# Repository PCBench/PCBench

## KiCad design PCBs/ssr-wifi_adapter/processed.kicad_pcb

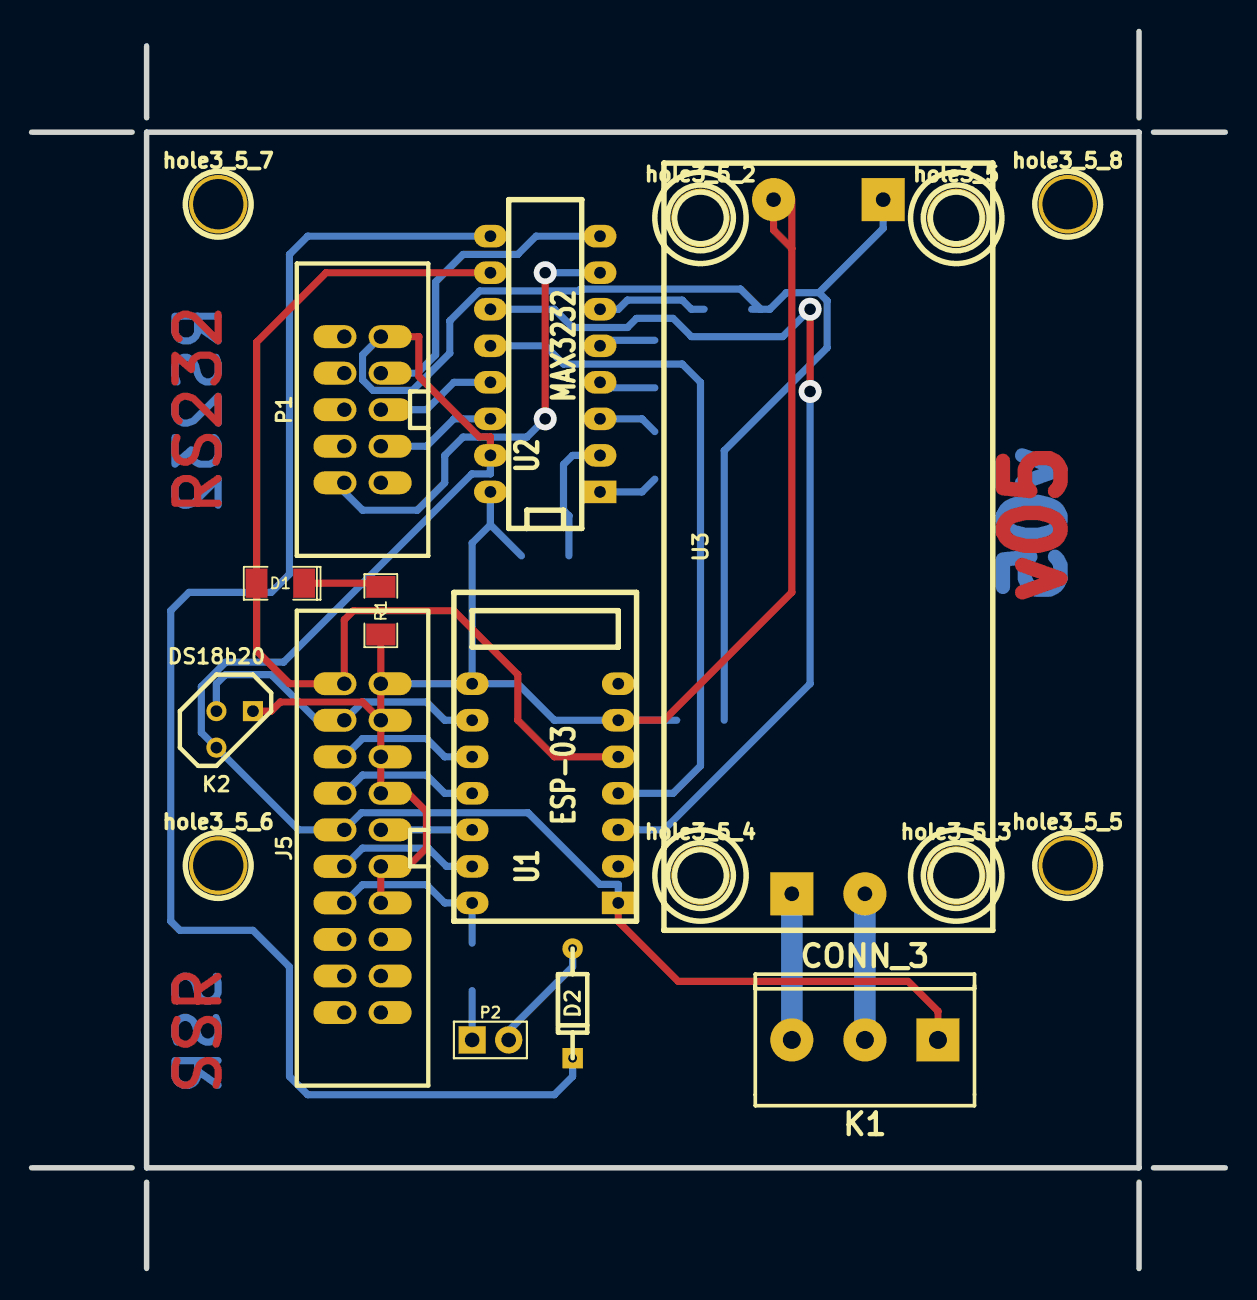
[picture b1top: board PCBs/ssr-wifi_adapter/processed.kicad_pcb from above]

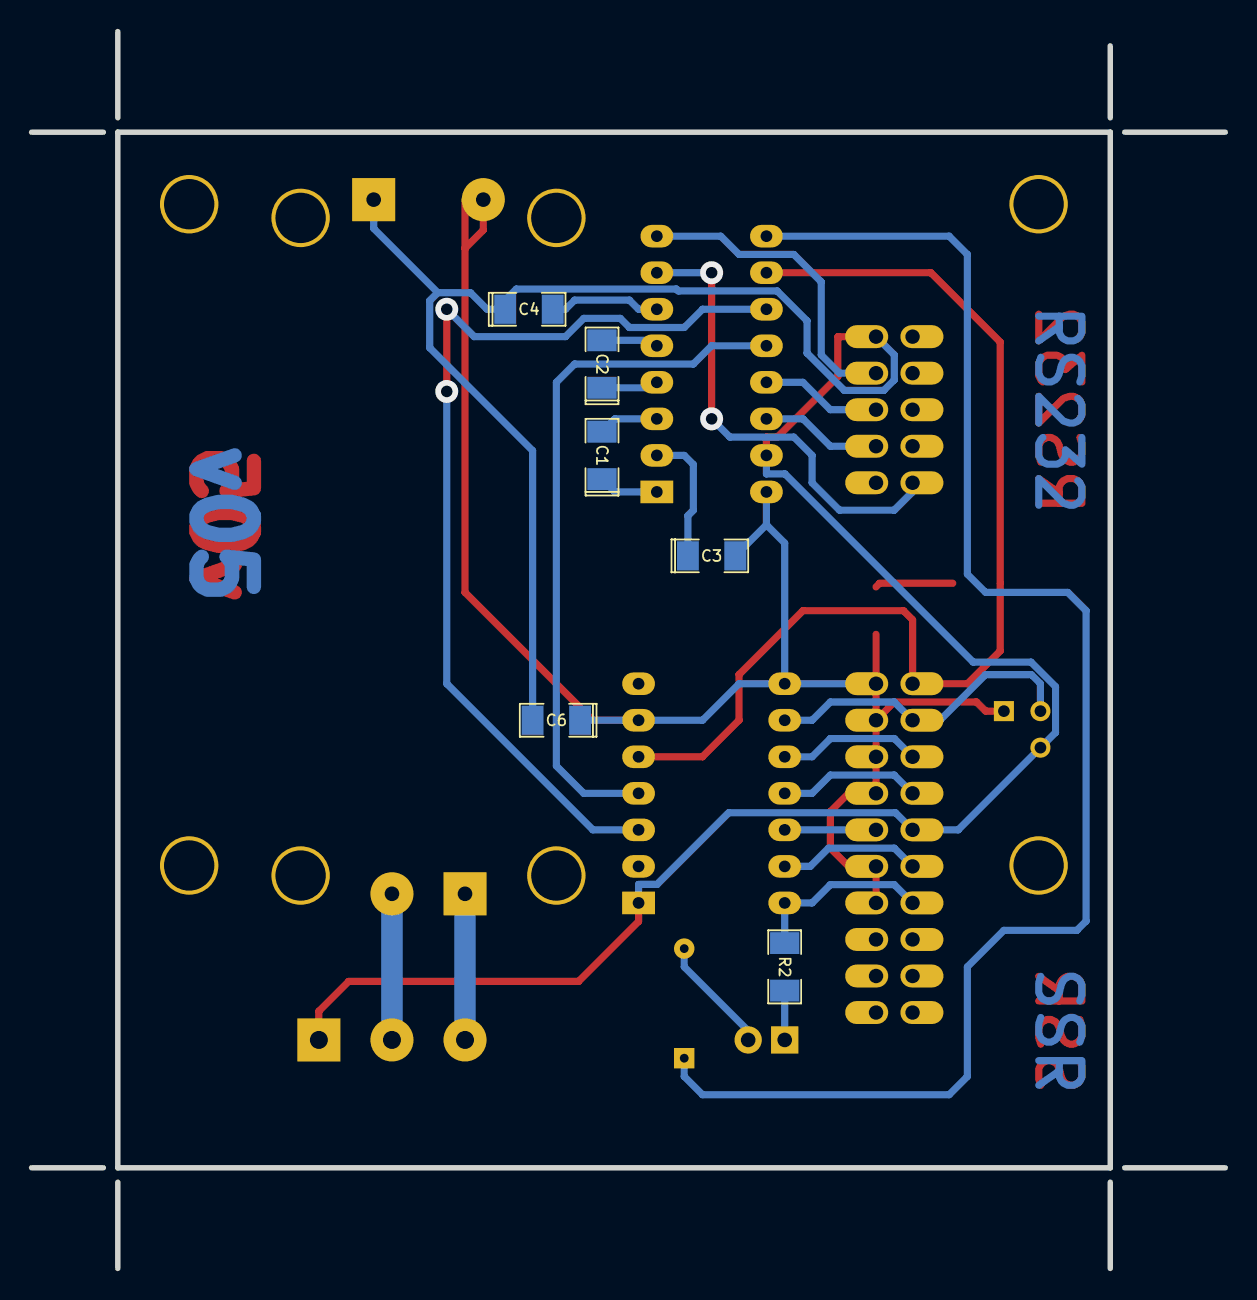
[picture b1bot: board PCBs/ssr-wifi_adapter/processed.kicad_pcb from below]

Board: 2 copper layers, 69.0 x 72.0 mm, 25 parts (6 on the bottom side), 27 nets.

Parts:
C1, C2, C3, C4, C6: 1uF; SM1206POL
D1: LED_RED; SM1206POL
D2: DIODESCH; DO-35
J5: CONN_10X2; conn_strip_10x2_largepads
K1: CONN_3; mors_3p
K2: DS18b20; TO92-123
P1: CONN_5X2; conn_strip_5x2_largepads
P2: FLASH; PIN_ARRAY_2X1
R1: 390; SM1206
R2: 47; SM1206
U1: ESP-03; ESP03BB
U2: MAX3232; DIP-16__300_ELL
U3: SWITCHER; SWITCHER_3V3_1A
hole3_5, hole3_5_2, hole3_5_3, hole3_5_4, hole3_5_5, hole3_5_6, hole3_5_7, hole3_5_8: 3.5mm; hole3_5

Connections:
+3.3V: C3.2, C6.1, J5.7, J5.9, J5.13, J5.15, J5.17, J5.19, K2.3, R1.2, U1.6, U1.8, U2.16, U3.3
/BOOT: D2.2, U2.9
/DSR: P1.2, U2.7
/DTR: P1.7, U2.8
/L: K1.3, U3.1
/LED: D1.2, J5.20, U1.5, U2.10
/N: K1.2, U3.2
/RXD: P1.3, U2.14
/SSR0: J5.8, R2.1, U1.14
/SSR1: J5.10, U1.13
/SSR2: J5.11, U1.12
/SSR3: J5.14, U1.11
/SSR4: J5.16, U1.10
/SSR5: J5.18, K2.2, U1.9
/TXD: P1.5, U2.13
/URXD: U1.4, U2.12
/UTXD: U1.3, U2.11
GND: C4.1, C6.2, J5.12, K1.1, K2.1, P1.9, U1.1, U2.15, U3.4
unnamed: D2.1, P2.2
unnamed: P2.1, R2.2
unnamed: D1.1, R1.1
unnamed: C2.1, U2.4
unnamed: C2.2, U2.5
unnamed: C3.1, U2.2
unnamed: C4.2, U2.6
unnamed: C1.1, U2.1
unnamed: C1.2, U2.3

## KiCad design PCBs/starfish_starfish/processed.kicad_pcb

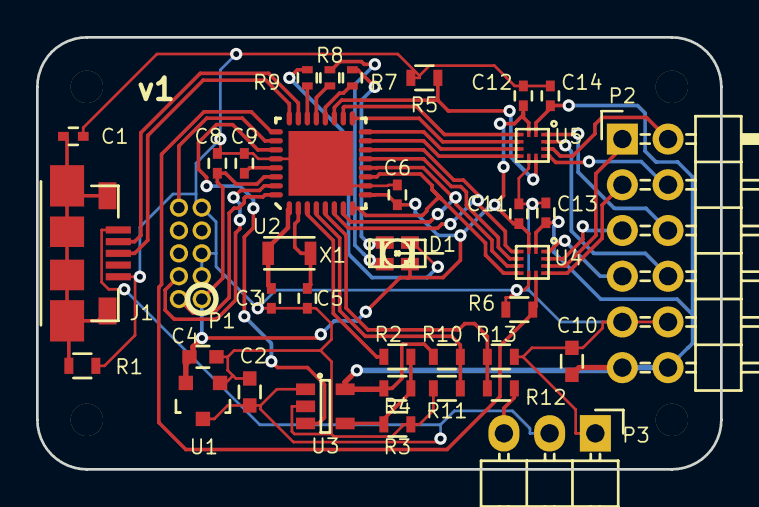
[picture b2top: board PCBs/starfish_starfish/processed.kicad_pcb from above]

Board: 2 copper layers, 38.0 x 24.0 mm, 37 parts (0 on the bottom side), 43 nets.

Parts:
C1, C3, C5: 10pF; C_0402
C2, C4, C10: 1uF; C_0603
C6, C8, C9, C11, C12, C13, C14: 100nF; C_0402
D1: LED-RGB-COMMON-ANODE; LED-1206-RGB
J1: microUSB; MICRO-USB-10104111
P1: CONN_02X05; CONN_02x05_0.05in
P2: CONN_6X2; Pin_Header_Angled_2x06
P3: CONN_3; Pin_Header_Angled_1x03
R1, R2, R10, R12: 47k; R_0603
R3, R4, R5, R6, R11, R13: 27k; R_0603
R7, R8, R9: 120; R_0402
U1: AP2120N; SOT-23
U2: SAMD21E15A-MU; QFP32
U3: TPS73101; SOT-23-5
U4, U5: FXMAR2104; UMLP-12
X1: CRYSTAL; FC-135

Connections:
+3V3: C4.1, C6.1, C8.1, C11.1, C12.1, D1.4, P1.1, U1.2, U2.9, U2.30, U4.2, U5.2
+5V: C2.1, J1.1, P3.2, U1.3, U3.1
/ADC: R12.2, R13.1, U2.5
/ADC_IN: P3.3, R12.1
/ADC_P: R10.2, R11.1, U2.4
/DAC: R4.1, U2.3
/EN_P: U2.27, U3.3
/EN_X: R6.1, U2.25, U4.8
/EN_Y: R5.1, U2.19, U5.8
/LED_B: R9.2, U2.22
/LED_G: R8.2, U2.21
/LED_R: R7.2, U2.20
/SWCLK: P1.4, U2.31
/SWDIO: P1.2, U2.32
/USB+: J1.3, U2.24
/USB-: J1.2, U2.23
/X1: P2.1, U4.10
/X1M: U2.7, U2.12, U4.5
/X2: P2.3, U4.9
/X2M: U2.8, U2.11, U4.6
/X3: P2.5, U4.11
/X3M: U2.13, U4.4
/X4: P2.7, U4.12
/X4M: U2.6, U2.14, U4.3
/Y1: P2.2, U5.10
/Y1M: U2.16, U5.5
/Y2: P2.4, U5.9
/Y2M: U2.15, U5.6
/Y3: P2.6, U5.12
/Y3M: U2.18, U5.3
/Y4: P2.8, U5.11
/Y4M: U2.17, U5.4
/~RESET: P1.10, U2.26
GND: C1.2, C2.2, C3.2, C4.2, C5.2, C6.2, C8.2, C9.2, C10.2, C11.2, C12.2, C13.2, C14.2, J1.5, P1.3, P1.5, P1.9, P2.9, P2.10, P3.1, R1.2, R3.2, R5.2, R6.2, R11.2, R13.2, U1.1, U2.0, U2.10, U2.28, U3.2, U4.7, U5.7
unnamed: C1.1, J1.0, R1.1
unnamed: C3.1, U2.1, X1.1
unnamed: C5.1, U2.2, X1.2
unnamed: C9.1, U2.29
unnamed: D1.1, R9.1
unnamed: D1.2, R7.1
unnamed: D1.3, R8.1
unnamed: R2.2, R3.1, R4.2, U3.4
VAA: C10.1, C13.1, C14.1, P2.11, P2.12, R2.1, R10.1, U3.5, U4.1, U5.1

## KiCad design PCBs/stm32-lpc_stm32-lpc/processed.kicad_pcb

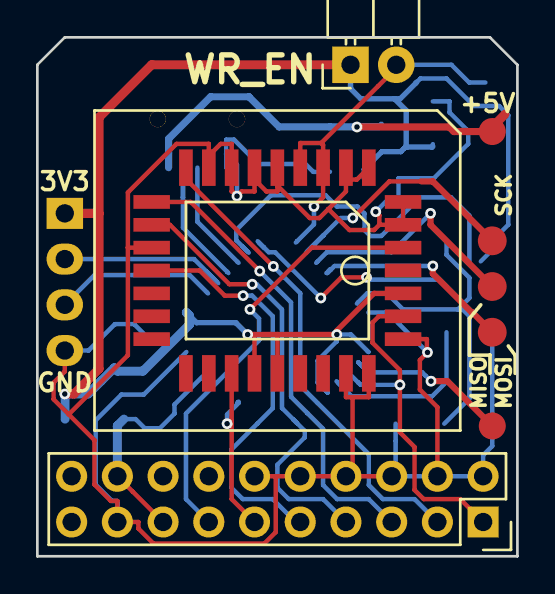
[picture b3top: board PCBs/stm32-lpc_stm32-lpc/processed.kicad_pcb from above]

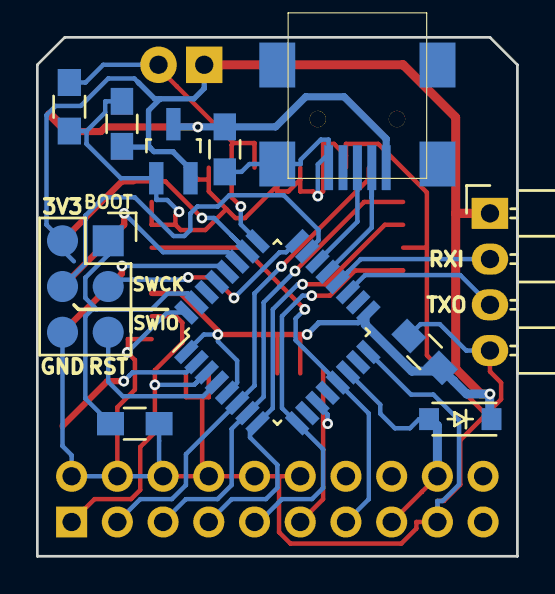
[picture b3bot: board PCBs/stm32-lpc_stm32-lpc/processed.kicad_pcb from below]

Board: 2 copper layers, 26.7 x 28.8 mm, 19 parts (11 on the bottom side), 24 nets.

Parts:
C1, C2, C3: 1u; C_0805_HandSoldering
CON1: SWD_BOOT_CS-6; Socket_Strip_Straight_2x03
D1: D_Schottky_Small; SOD-123
JP1: JUMPER; Pin_Header_Angled_1x02
P1: CONN_02X10; Socket_Strip_Straight_2x10
P2: CONN_01X04; Pin_Header_Angled_1x04
P3: USB_OTG; USB-MINI-B-SMD
P4, P5, P6, P7, P8: CONN_01X01; TSTPT
R1, R2: 4k7; R_0805_HandSoldering
U1: Pm49FL004; PLCC-32
U2: STM32F042Kx; LQFP-32_7x7mm_Pitch0.8mm
U3: MCP1700; SOT-23_Handsoldering

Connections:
/3V3IN: D1.2, P1.15, P1.18, U2.14
/BOOT0: CON1.1, R2.1, U2.31
/CLK: P1.1, U1.31, U2.3
/D0: P1.3, U1.13, U2.6
/D1: P1.5, U1.14, U2.7
/D2: P1.7, U1.15, U2.8
/D3: P1.9, U1.17, U2.9
/D+: P3.3, U2.22
/D-: P3.2, U2.21
/MISO: P5.1, U2.27
/MOSI: P4.1, U2.28
/RXD: P2.2, U2.20
/SCK: P6.1, U2.26
/SPIOE: P7.1, U2.2
/SWCLK: CON1.3, U2.24
/SWDIO: CON1.4, U2.23
/TXD: P2.3, U2.19
/VBUS: C2.1, P3.1, P8.1, U3.3
/~LFRAME: P1.11, U1.23, U2.11
/~RST: P1.13, U1.2, U2.13
/~SRST: CON1.5, U2.4
/~WP: JP1.2, R1.1, U1.7, U1.8, U2.25
GND: C1.2, C2.2, C3.2, CON1.6, P1.2, P1.4, P1.6, P1.8, P1.10, P1.12, P1.17, P2.4, P3.5, P3.6, R1.2, R2.2, U1.3, U1.4, U1.5, U1.6, U1.9, U1.10, U1.11, U1.12, U1.16, U1.28, U1.29, U1.30, U2.16, U2.32, U3.1
VCC: C1.1, C3.1, CON1.2, D1.1, JP1.1, P2.1, U1.24, U1.25, U1.32, U2.1, U2.5, U2.17, U3.2

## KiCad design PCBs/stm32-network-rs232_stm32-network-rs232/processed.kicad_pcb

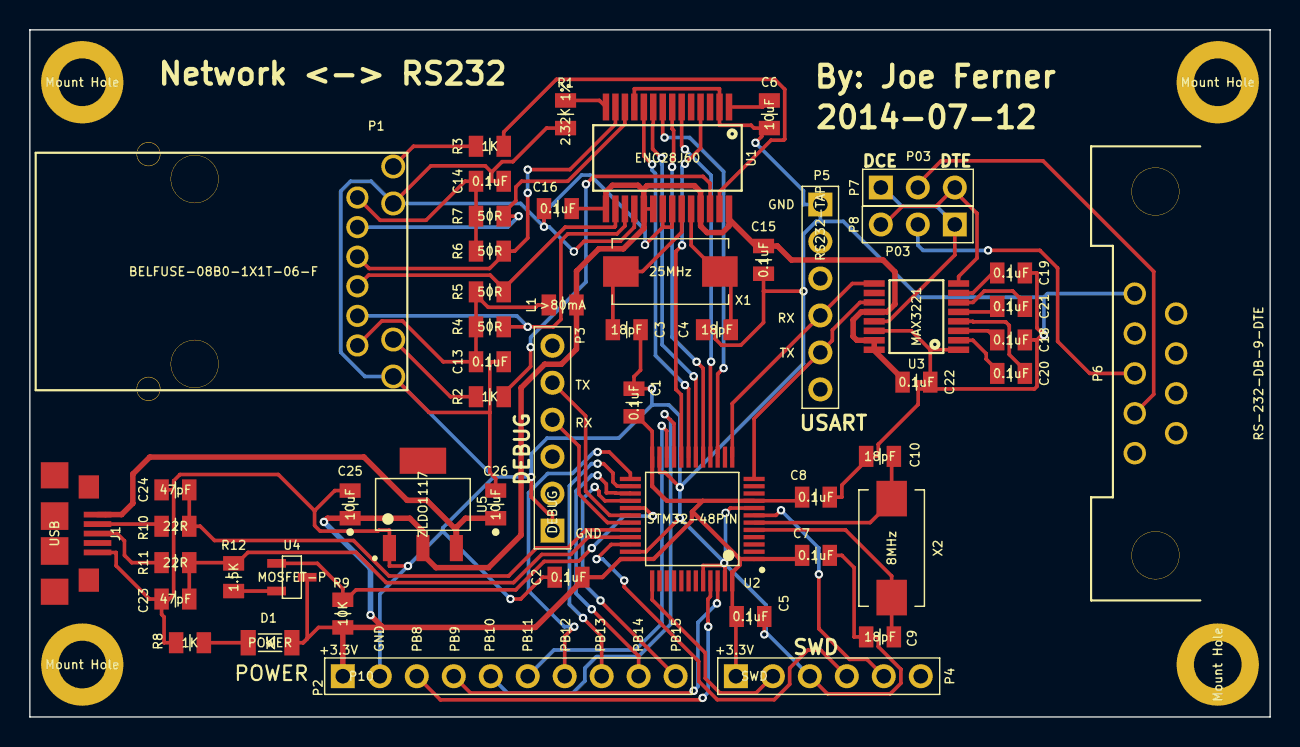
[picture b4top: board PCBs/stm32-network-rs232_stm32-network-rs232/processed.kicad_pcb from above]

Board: 2 copper layers, 85.2 x 47.2 mm, 57 parts (0 on the bottom side), 57 nets.

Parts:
C1, C2, C5, C7, C8, C13, C14, C15, C16, C18, C19, C20, C21, C22: 0.1uF; CAPC2012X100N
C3, C4, C9, C10: 18pF; CAPC2012X100N
C6: 10uF; CAPC2012X100N
C23, C24: 47pF; CAPC2012X100N
C25, C26: 10uF; CAPCP2012X100N
D1: POWER; LEDC3216X100N
J1: USB; JST_UB-MC5BR3-SD204-4S-NMP
L1: >80mA; RESC2012X100N
M1, M2, M3, M4: Mount Hole; MTGNP565H328Z565P
P1: BELFUSE-08B0-1X1T-06-F; BEL-FUSE-08B0-1X1T-06-F
P2: P10; HDRV10W66P254_1X10_1006X249X838P
P3: DEBUG; HDRV6W66P254_1X6_1524X249X838P
P4: SWD; HDRV6W66P254_1X6_1524X249X838P
P5: RS232-TAP; HDRV6W66P254_1X6_1524X249X838P
P6: RS-232-DB-9-DTE; TECONN-5747840-2
P7, P8: P03; HDRV3W66P254_1X3_762X249X838P
R1: 2.32K 1%; RESC2012X100N
R2, R3, R8: 1K; RESC2012X100N
R4, R5, R6, R7: 50R; RESC2012X100N
R9: 10K; RESC2012X100N
R10, R11: 22R; RESC2012X100N
R12: 1.5K; RESC2012X100N
U1: ENC28J60; SOP65P780X200-28N
U2: STM32-48PIN; QFP50P900X900X160-48N
U3: MAX3221; SOP65P640X120-16N
U4: MOSFET-P; SOT95P237X112_123-3N
U5: ZLDO1117; SOT230P700X180-4N
X1: 25MHz; XTAL8045X200N
X2: 8MHz; XTAL8045X200N

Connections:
+3.3V: C1.2, C2.2, C5.2, C7.2, C8.2, C15.2, C16.2, C22.1, C25.1, D1.1, L1.1, P2.1, P4.1, R9.2, U1.15, U1.19, U1.20, U1.25, U1.28, U2.1, U2.9, U2.24, U2.36, U2.48, U3.12, U3.15, U3.16, U4.3, U5.2
+5V: C26.1, J1.1, U5.3
/DB9RX: P6.2, P7.2
/DB9TX: P6.3, P8.2
/ENC28J60CS: U1.9, U2.18
/ENC28J60INT: U1.4, U2.20
/ENC28J60RESET: U1.10, U2.19
/RS232RX: P7.3, P8.3, U3.8
/RS232TX: P7.1, P8.1, U3.13
/SPIMISO: U1.6, U2.16
/SPIMOSI: U1.7, U2.17
/SPISCK: U1.8, U2.15
/SWCLK: P4.2, U2.37
/SWDIO: P4.4, U2.34
/USART1RX: P3.4, U2.31
/USART1TX: P3.5, U2.30
/USART2RX: P5.4, U2.13, U3.9
/USART2TX: P5.5, U2.12, U3.11
/USBDIS: R9.1, U2.29, U4.1
/USBDM: C24.1, R10.1, U2.32
/USBDP: C23.1, R11.1, R12.1, U2.33
/nRST: P4.5, U2.7
GNDPWR: C1.1, C2.1, C3.2, C4.2, C5.1, C6.2, C7.1, C8.1, C9.2, C10.2, C13.1, C14.1, C15.1, C16.1, C18.2, C19.2, C22.2, C23.2, C24.2, C25.2, C26.2, J1.5, P1.7, P1.9, P2.2, P3.1, P4.3, P5.1, P6.5, R1.1, R8.1, U1.2, U1.11, U1.18, U1.21, U1.22, U2.8, U2.23, U2.35, U2.44, U2.47, U3.1, U3.14, U5.1
unnamed: C3.1, U1.23, X1.1
unnamed: C4.1, U1.24, X1.2
unnamed: C6.1, U1.1
unnamed: C9.1, U2.5, X2.1
unnamed: C10.1, U2.6, X2.2
unnamed: C13.2, L1.2, P1.1, R4.1, R5.2
unnamed: C14.2, P1.6, R6.1, R7.2
unnamed: C18.1, U3.3
unnamed: C19.1, U3.7
unnamed: C20.1, U3.2
unnamed: C20.2, U3.4
unnamed: C21.1, U3.5
unnamed: C21.2, U3.6
unnamed: D1.2, R8.2
unnamed: J1.2, R10.2
unnamed: J1.3, R11.2
unnamed: P1.2, R4.2, U1.17
unnamed: P1.3, R5.1, U1.16
unnamed: P1.4, R6.2, U1.13
unnamed: P1.5, R7.1, U1.12
unnamed: P1.8, R2.2
unnamed: P1.10, R3.2
unnamed: P2.3, U2.45
unnamed: P2.4, U2.46
unnamed: P2.5, U2.21
unnamed: P2.6, U2.22
unnamed: P2.7, U2.25
unnamed: P2.8, U2.26
unnamed: P2.9, U2.27
unnamed: P2.10, U2.28
unnamed: R1.2, U1.14
unnamed: R2.1, U1.26
unnamed: R3.1, U1.27
unnamed: R12.2, U4.2

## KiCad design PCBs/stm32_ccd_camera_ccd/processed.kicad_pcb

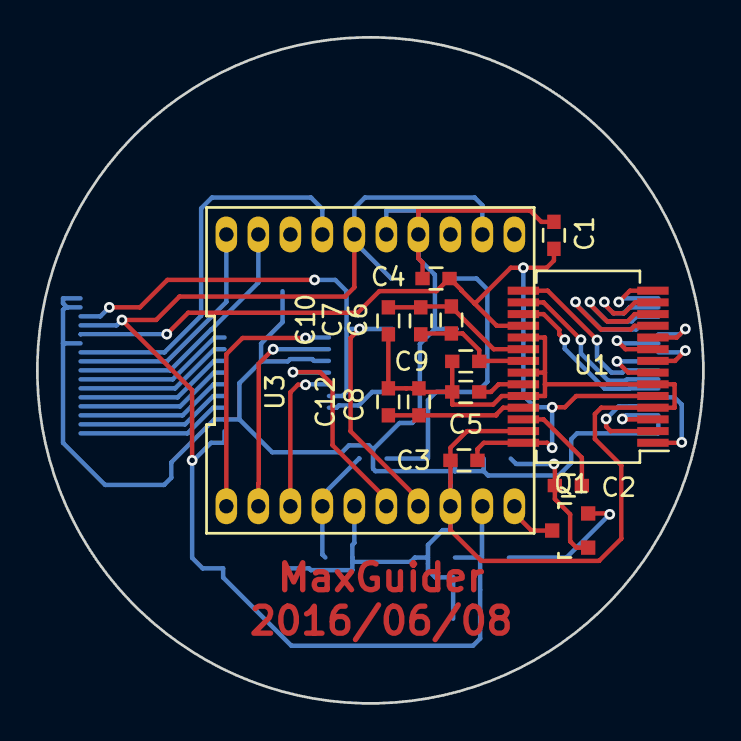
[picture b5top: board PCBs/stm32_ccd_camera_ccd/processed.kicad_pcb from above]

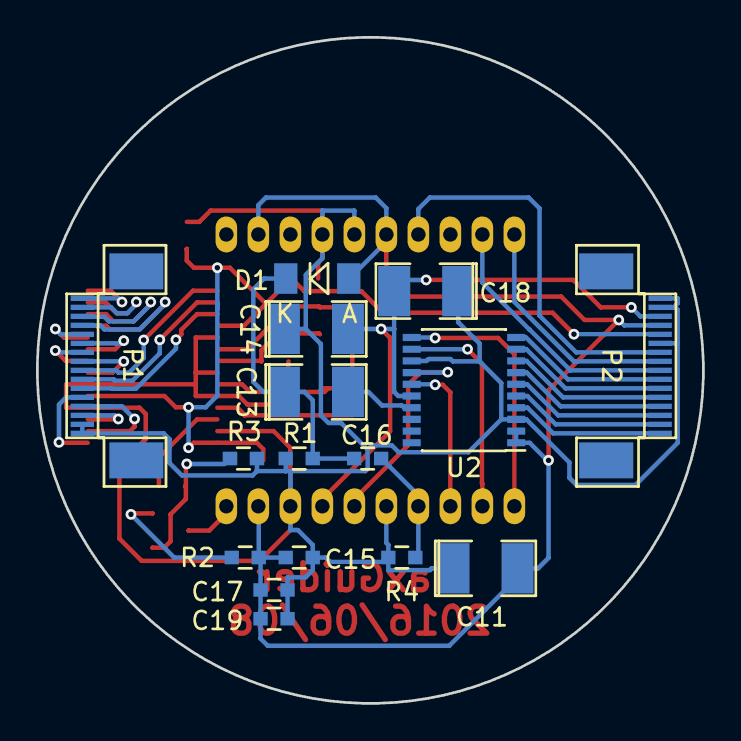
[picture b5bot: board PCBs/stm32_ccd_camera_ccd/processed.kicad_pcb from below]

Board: 2 copper layers, 37.0 x 37.0 mm, 30 parts (16 on the bottom side), 43 nets.

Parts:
C1, C2, C3, C4, C5, C6, C8, C9, C10: 0.1; C_0603
C7: 10; C_0603
C11, C18: 3.3/16V; SMD-1210_Pol
C12, C16: 1; C_0603
C13: 1/35V; SMD-1210_Pol
C14: 22/16V; SMD-1210_Pol
C15, C19: 0.01; C_0603
C17: 3.3/20V; C_0603
D1: D_Small; MiniMELF_Standard
P1, P2: CONN_01X16; FPC_16
Q1: BF862; SOT-23
R1: 100K; C_0603
R2: 100; C_0603
R3: 3.9K; C_0603
R4: 1M; C_0603
U1: AD9826; SSOP-28_5.3x10.2mm_Pitch0.65mm
U2: CXD1267AN; SSOP-20_4.4x6.5mm_Pitch0.65mm
U3: ICX429AL

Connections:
+5V: C1.1, C3.1, C4.2, P2.5, U1.5, U1.18, U1.28
/+15V: C11.2, C15.1, C17.2, C19.2, D1.2, P2.4, R2.2, U2.1, U2.2, U3.9, U3.12, U3.16
/-9V: C14.2, C18.2, P2.3, U2.16, U3.7
/SCLK: P1.7, U1.16
/SDATA: P1.8, U1.15
/SLOAD: P1.6, U1.17
GND: C1.2, C3.2, C4.1, C5.2, C8.2, C9.2, C10.2, C11.1, C12.2, C14.1, C15.2, C17.1, C18.1, C19.1, P1.1, P1.2, P2.1, P2.2, P2.6, R1.2, R3.1, R4.2, U1.4, U1.6, U1.19, U1.22, U1.24, U1.27, U2.3, U2.13, U3.5, U3.8, U3.14, U3.15
unnamed: C2.1, U1.26
unnamed: C2.2, Q1.1, R3.2
unnamed: C5.1, U1.23
unnamed: C6.1, C7.1, C9.1, U1.21
unnamed: C6.2, C7.2, C10.1, U1.20
unnamed: C8.1, C12.1, U1.25
unnamed: C13.1, C16.2, D1.1, R1.1
unnamed: C13.2, U2.17
unnamed: C16.1, R4.1, U3.4
unnamed: P1.3, U1.3
unnamed: P1.4, U1.2
unnamed: P1.5, U1.1
unnamed: P1.9, U1.7
unnamed: P1.10, U1.8
unnamed: P1.11, U1.9
unnamed: P1.12, U1.10
unnamed: P1.13, U1.11
unnamed: P1.14, U1.12
unnamed: P1.15, U1.13
unnamed: P1.16, U1.14
unnamed: P2.7, U3.17
unnamed: P2.8, U3.20
unnamed: P2.9, U3.19
unnamed: P2.10, U2.10
unnamed: P2.11, U2.9
unnamed: P2.12, U2.8
unnamed: P2.13, U2.7
unnamed: P2.14, U2.6
unnamed: P2.15, U2.5
unnamed: P2.16, U2.4
unnamed: Q1.2, R2.1
unnamed: Q1.3, U3.10
unnamed: U2.11, U3.1
unnamed: U2.12, U3.2
unnamed: U2.14, U3.6
unnamed: U2.15, U3.3

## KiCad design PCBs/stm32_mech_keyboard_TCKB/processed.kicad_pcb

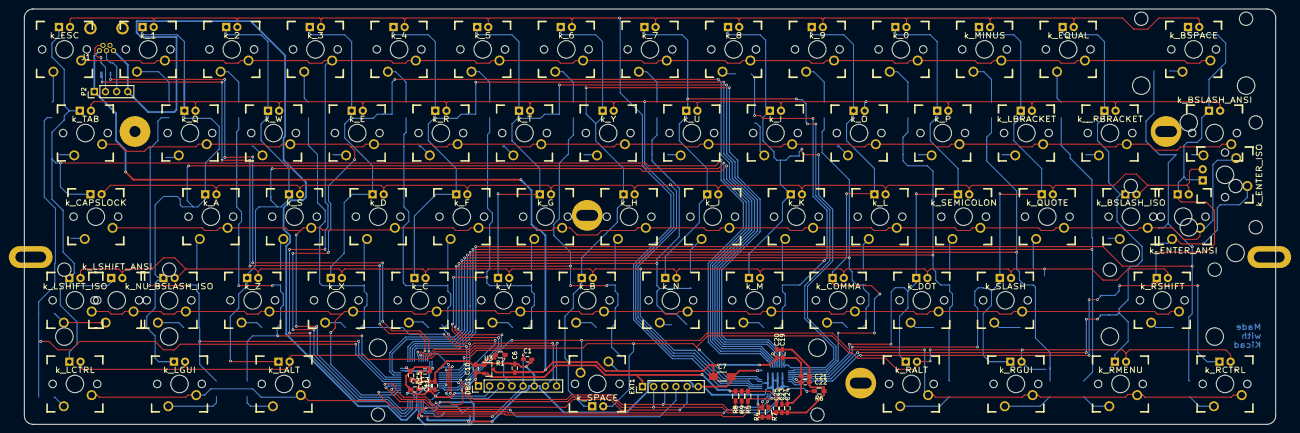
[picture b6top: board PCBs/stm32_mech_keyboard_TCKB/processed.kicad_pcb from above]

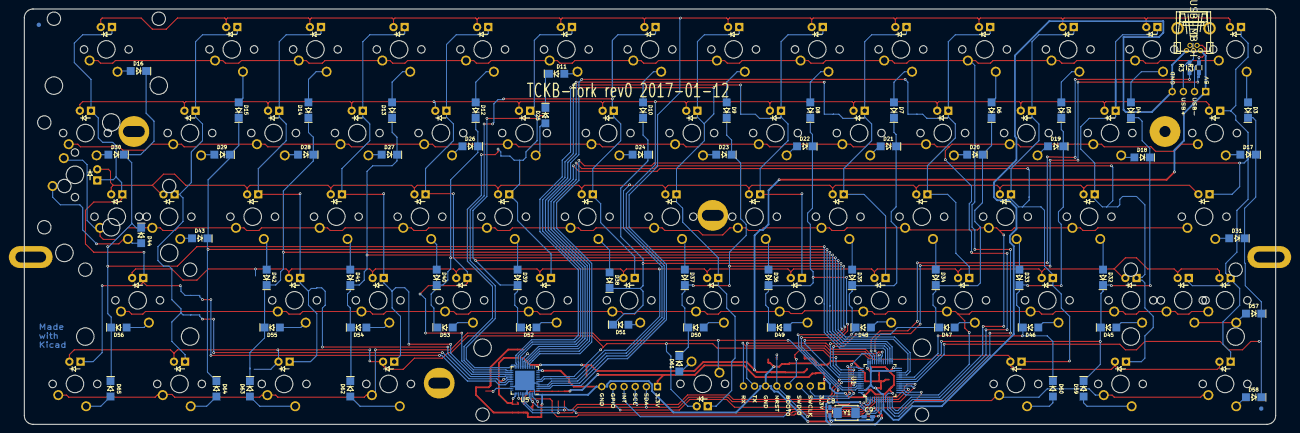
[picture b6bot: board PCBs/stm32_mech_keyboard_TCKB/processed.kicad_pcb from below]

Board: 2 copper layers, 285.0 x 94.6 mm, 242 parts (74 on the bottom side), 124 nets.

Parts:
C1, C2, C3, C4, C5, C11, C20, C21, C23: 100nF; C_0603_HandSoldering
C6, C10: 1uF; C_0603_HandSoldering
C7: 22uF; C_1206_HandSoldering
C8, C9: 22pF; C_0603_HandSoldering
C19, C22, C24, C25: 470nF; C_0603_HandSoldering
D3, D4, D5, D6, D7, D8, D9, D10, D11, D12, D13, D14, D15, D16, D17, D18, D19, D20, D21, D22, D23, D24, D25, D26, D27, D28, D29, D30, D31, D32, D33, D34, D35, D36, D37, D38, D39, D40, D41, D42, D43, D44, D45, D46, D47, D48, D49, D50, D51, D52, D53, D54, D55, D56, D57, D58, D59, D60, D61, D62, D63, D64, D65: 1N4148; MiniMELF_2mm
DBG1: STRIP_8P; Pin_Header_Straight_1x08_Pitch2.54mm
EXT1: CONN_01X06; Pin_Header_Straight_1x06_Pitch2.54mm
FID: FIDUCIAL
FID_2: FIDUCIAL
HOLE: VAL**; PKRHC
HOLE_2, HOLE_3, HOLE_4: VAL**; PKRH
HOLE_5, HOLE_6: VAL**; PKRHSL
J1: USB-MB-H
LED1: led_ESC; CHERRY_MX_LED
LED2: led_TAB; CHERRY_MX_LED
LED3: led_LSHIFT_ISO; CHERRY_MX_LED
LED4: led_LSHIFT_ANSI; CHERRY_MX_LED
LED5: led_LCTRL; CHERRY_MX_LED
LED6: led_1; CHERRY_MX_LED
LED7: led_Q; CHERRY_MX_LED
LED8: led_A; CHERRY_MX_LED
LED9: led_NU_BSLASH_ISO; CHERRY_MX_LED
LED10: led_LGUI; CHERRY_MX_LED
LED11: led_2; CHERRY_MX_LED
LED12: led_W; CHERRY_MX_LED
LED13: led_S; CHERRY_MX_LED
LED14: led_Z; CHERRY_MX_LED
LED15: led_LALT; CHERRY_MX_LED
LED16: led_3; CHERRY_MX_LED
LED17: led_E; CHERRY_MX_LED
LED18: led_D; CHERRY_MX_LED
LED19: led_X; CHERRY_MX_LED
LED20: led_4; CHERRY_MX_LED
LED21: led_R; CHERRY_MX_LED
LED22: led_F; CHERRY_MX_LED
LED23: led_C; CHERRY_MX_LED
LED24: led_5; CHERRY_MX_LED
LED25: led_T; CHERRY_MX_LED
LED26: led_G; CHERRY_MX_LED
LED27: led_V; CHERRY_MX_LED
LED28: led_6; CHERRY_MX_LED
LED29: led_Y; CHERRY_MX_LED
LED30: led_H; CHERRY_MX_LED
LED31: led_B; CHERRY_MX_LED
LED32: led_SPACE; CHERRY_MX_LED
LED33: led_7; CHERRY_MX_LED
LED34: led_U; CHERRY_MX_LED
LED35: led_J; CHERRY_MX_LED
LED36: led_N; CHERRY_MX_LED
LED37: led_8; CHERRY_MX_LED
LED38: led_I; CHERRY_MX_LED
LED39: led_K; CHERRY_MX_LED
LED40: led_M; CHERRY_MX_LED
LED41: led_9; CHERRY_MX_LED
LED42: led_O; CHERRY_MX_LED
LED43: led_L; CHERRY_MX_LED
LED44: led_COMMA; CHERRY_MX_LED
LED45: led_0; CHERRY_MX_LED
LED46: led_P; CHERRY_MX_LED
LED47: led_SEMICOLON; CHERRY_MX_LED
LED48: led_DOT; CHERRY_MX_LED
LED49: led_RALT; CHERRY_MX_LED
LED50: led_MINUS; CHERRY_MX_LED
LED51: led_LBRACKET; CHERRY_MX_LED
LED52: led_QUOTE; CHERRY_MX_LED
LED53: led_SLASH; CHERRY_MX_LED
LED54: led_RGUI; CHERRY_MX_LED
LED55: led_EQUAL; CHERRY_MX_LED
LED56: led_RBRACKET; CHERRY_MX_LED
LED57: led_BSLASH_ISO; CHERRY_MX_LED
LED58: led_RMENU; CHERRY_MX_LED
LED59: led_BSPACE; CHERRY_MX_LED
LED60: led_BSLASH_ANSI; CHERRY_MX_LED
LED61: led_ENTER_ISO; CHERRY_MX_LED
LED62: led_ENTER_ANSI; CHERRY_MX_LED
LED63: led_RSHIFT; CHERRY_MX_LED
LED64: led_RCTRL; CHERRY_MX_LED
LED65: led_CAPSLOCK; CHERRY_MX_LED
P2: CONN_01X04; Pin_Header_Straight_1x04_Pitch2.54mm
R1: 220r; R_0603_HandSoldering
R2, R3: 22r; R_0603_HandSoldering
R4, R5, R7: 100k; R_0603_HandSoldering
R6: 20k; R_0603_HandSoldering
R8, R9: 1k; R_0603_HandSoldering
ST1: Backspace_2U; CHERRY_PCB_200H_STAB
ST2: ANSI_Return_2.25U; CHERRY_PCB_225H_STAB
ST3: ISO_Return_2U; CHERRY_PCB_200H_STAB
ST4: Right_Shift_2.75U; CHERRY_PCB_275H_STAB
ST5: ANSI_Left_Shift_2.25U; CHERRY_PCB_225H_STAB
ST6: Space_6.25U; CHERRY_PCB_625H_STAB
SW3: k_ESC; CHERRY_PCB_100H
SW4: k_1; CHERRY_PCB_100H
SW5: k_2; CHERRY_PCB_100H
SW6: k_3; CHERRY_PCB_100H
SW7: k_4; CHERRY_PCB_100H
SW8: k_5; CHERRY_PCB_100H
SW9: k_6; CHERRY_PCB_100H
SW10: k_7; CHERRY_PCB_100H
SW11: k_8; CHERRY_PCB_100H
SW12: k_9; CHERRY_PCB_100H
SW13: k_0; CHERRY_PCB_100H
SW14: k_MINUS; CHERRY_PCB_100H
SW15: k_EQUAL; CHERRY_PCB_100H
SW16: k_BSPACE; CHERRY_PCB_200H_SW
SW17: k_TAB; CHERRY_PCB_150H
SW18: k_Q; CHERRY_PCB_100H
SW19: k_W; CHERRY_PCB_100H
SW20: k_E; CHERRY_PCB_100H
SW21: k_R; CHERRY_PCB_100H
SW22: k_T; CHERRY_PCB_100H
SW23: k_Y; CHERRY_PCB_100H
SW24: k_U; CHERRY_PCB_100H
SW25: k_I; CHERRY_PCB_100H
SW26: k_O; CHERRY_PCB_100H
SW27: k_P; CHERRY_PCB_100H
SW28: k_LBRACKET; CHERRY_PCB_100H
SW29: k__RBRACKET; CHERRY_PCB_100H
SW30: k_BSLASH_ANSI; CHERRY_PCB_150H
SW31: k_CAPSLOCK; CHERRY_PCB_175H
SW32: k_A; CHERRY_PCB_100H
SW33: k_S; CHERRY_PCB_100H
SW34: k_D; CHERRY_PCB_100H
SW35: k_F; CHERRY_PCB_100H
SW36: k_G; CHERRY_PCB_100H
SW37: k_H; CHERRY_PCB_100H
SW38: k_J; CHERRY_PCB_100H
SW39: k_K; CHERRY_PCB_100H
SW40: k_L; CHERRY_PCB_100H
SW41: k_SEMICOLON; CHERRY_PCB_100H
SW42: k_QUOTE; CHERRY_PCB_100H
SW43: k_BSLASH_ISO; CHERRY_PCB_100H
SW44: k_ENTER_ISO; CHERRY_PCB_200H_SW
SW45: k_ENTER_ANSI; CHERRY_PCB_225H_SW
SW46: k_LSHIFT_ISO; CHERRY_PCB_125H
SW47: k_NU_BSLASH_ISO; CHERRY_PCB_100H
SW48: k_Z; CHERRY_PCB_100H
SW49: k_X; CHERRY_PCB_100H
SW50: k_C; CHERRY_PCB_100H
SW51: k_V; CHERRY_PCB_100H
SW52: k_B; CHERRY_PCB_100H
SW53: k_N; CHERRY_PCB_100H
SW54: k_M; CHERRY_PCB_100H
SW55: k_COMMA; CHERRY_PCB_100H
SW56: k_DOT; CHERRY_PCB_100H
SW57: k_SLASH; CHERRY_PCB_100H
SW58: k_RSHIFT; CHERRY_PCB_275H_SW
SW59: k_LSHIFT_ANSI; CHERRY_PCB_225H_SW
SW60: k_LCTRL; CHERRY_PCB_125H
SW61: k_LGUI; CHERRY_PCB_125H
SW62: k_LALT; CHERRY_PCB_125H
SW63: k_SPACE; CHERRY_PCB_625H_SW
SW64: k_RALT; CHERRY_PCB_125H
SW65: k_RGUI; CHERRY_PCB_125H
SW66: k_RMENU; CHERRY_PCB_125H
SW67: k_RCTRL; CHERRY_PCB_125H
U1: STM32F042C6Tx; LQFP-48_7x7mm_Pitch0.5mm
U3: MCP1700T-3002E/TT; SOT-23
U5: IS31FL3733; UQFN-48-1EP_6x6mm_Pitch0.4mm
Y1: Crystal; ABM3

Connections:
+3V3: C2.1, C3.1, C4.1, C5.1, C10.1, C11.1, C25.1, DBG1.1, EXT1.1, R5.1, R8.1, R9.1, U1.1, U1.9, U1.24, U1.36, U1.48, U3.2, U5.39
+5V: C6.1, C7.1, C19.1, C20.1, C21.1, C22.1, C23.1, C24.1, J1.VBUS, P2.1, U3.3, U5.20, U5.29, U5.37, U5.38
/Led_Controller/RSET: R6.1, U5.35
BOOT0: DBG1.4, R1.1, U1.44
Col_0_: D3.1, D17.1, D31.1, D57.1, D58.1, U1.18
Col_1_: D4.1, D18.1, D32.1, D45.1, D59.1, U1.19
Col_2_: D5.1, D19.1, D33.1, D46.1, D60.1, U1.20
Col_3_: D6.1, D20.1, D34.1, D47.1, U1.39
Col_4_: D7.1, D21.1, D35.1, D48.1, U1.40
Col_5_: D8.1, D22.1, D36.1, D49.1, U1.41
Col_6_: D9.1, D23.1, D37.1, D50.1, D61.1, U1.45
Col_7_: D10.1, D24.1, D38.1, D51.1, U1.46
Col_8_: D11.1, D25.1, D39.1, D52.1, U1.21
Col_9_: D12.1, D26.1, D40.1, D53.1, U1.22
Col_10_: D13.1, D27.1, D41.1, D54.1, D62.1, U1.25
Col_11_: D14.1, D28.1, D42.1, D55.1, D63.1, U1.26
Col_12_: D15.1, D29.1, D43.1, D64.1, U1.27
Col_13_: D16.1, D30.1, D44.1, D56.1, D65.1, U1.28
EXT_GPIO: EXT1.5, U1.2
EXT_INT: EXT1.4, U1.17
GNDPWR: C1.2, C2.2, C3.2, C4.2, C5.2, C6.2, C7.2, C8.2, C9.2, C10.2, C11.2, C19.2, C20.2, C21.2, C22.2, C23.2, C24.2, C25.2, DBG1.6, EXT1.6, J1.GND, P2.4, R1.2, R4.2, R6.2, R7.2, U1.8, U1.23, U1.35, U1.47, U3.1, U5.5, U5.12, U5.34, U5.43, U5.44, U5.48, U5.49
LED_COL_0: LED1.2, LED2.2, LED3.2, LED4.2, LED5.2, LED65.2, U5.16
LED_COL_1: LED6.2, LED7.2, LED8.2, LED9.2, LED10.2, U5.17
LED_COL_2: LED11.2, LED12.2, LED13.2, LED14.2, LED15.2, U5.18
LED_COL_3: LED16.2, LED17.2, LED18.2, LED19.2, U5.19
LED_COL_4: LED20.2, LED21.2, LED22.2, LED23.2, U5.21
LED_COL_5: LED24.2, LED25.2, LED26.2, LED27.2, U5.22
LED_COL_6: LED28.2, LED29.2, LED30.2, LED31.2, LED32.2, U5.23
LED_COL_7: LED33.2, LED34.2, LED35.2, LED36.2, U5.24
LED_COL_8: LED37.2, LED38.2, LED39.2, LED40.2, U5.25
LED_COL_9: LED41.2, LED42.2, LED43.2, LED44.2, U5.26
LED_COL_10: LED45.2, LED46.2, LED47.2, LED48.2, LED49.2, U5.27
LED_COL_11: LED50.2, LED51.2, LED52.2, LED53.2, LED54.2, U5.28
LED_COL_12: LED55.2, LED56.2, LED57.2, LED58.2, U5.30
LED_COL_13: LED59.2, LED60.2, LED61.2, LED62.2, LED63.2, LED64.2, U5.31
LED_INT: R5.2, U1.16, U5.45
LED_LINE_0: LED1.1, LED6.1, LED11.1, LED16.1, LED20.1, LED24.1, LED28.1, LED33.1, LED37.1, LED41.1, LED45.1, LED50.1, LED55.1, LED59.1, U5.2
LED_LINE_1: LED2.1, LED7.1, LED12.1, LED17.1, LED21.1, LED25.1, LED29.1, LED34.1, LED38.1, LED42.1, LED46.1, LED51.1, LED56.1, LED60.1, U5.3
LED_LINE_2: LED8.1, LED13.1, LED18.1, LED22.1, LED26.1, LED30.1, LED35.1, LED39.1, LED43.1, LED47.1, LED52.1, LED57.1, LED61.1, LED62.1, LED65.1, U5.4
LED_LINE_3: LED3.1, LED4.1, LED9.1, LED14.1, LED19.1, LED23.1, LED27.1, LED31.1, LED36.1, LED40.1, LED44.1, LED48.1, LED53.1, LED63.1, U5.6
LED_LINE_4: LED5.1, LED10.1, LED15.1, LED32.1, LED49.1, LED54.1, LED58.1, LED64.1, U5.7
LED_SHTDN: R7.1, U1.15, U5.46
Line_0_: SW3.2, SW4.2, SW5.2, SW6.2, SW7.2, SW8.2, SW9.2, SW10.2, SW11.2, SW12.2, SW13.2, SW14.2, SW15.2, SW16.2, U1.10
Line_1_: SW17.2, SW18.2, SW19.2, SW20.2, SW21.2, SW22.2, SW23.2, SW24.2, SW25.2, SW26.2, SW27.2, SW28.2, SW29.2, SW30.2, U1.11
Line_2_: SW31.2, SW32.2, SW33.2, SW34.2, SW35.2, SW36.2, SW37.2, SW38.2, SW39.2, SW40.2, SW41.2, SW42.2, SW43.2, SW44.2, SW45.2, U1.12
Line_3_: SW46.2, SW47.2, SW48.2, SW49.2, SW50.2, SW51.2, SW52.2, SW53.2, SW54.2, SW55.2, SW56.2, SW57.2, SW58.2, SW59.2, U1.13
Line_4_: SW60.2, SW61.2, SW62.2, SW63.2, SW64.2, SW65.2, SW66.2, SW67.2, U1.14
NRST: C1.1, DBG1.5, U1.7
unnamed: D3.2, SW3.1
unnamed: D4.2, SW4.1
unnamed: D5.2, SW5.1
unnamed: D6.2, SW6.1
unnamed: D7.2, SW7.1
unnamed: D8.2, SW8.1
unnamed: D9.2, SW9.1
unnamed: D10.2, SW10.1
unnamed: D11.2, SW11.1
unnamed: D12.2, SW12.1
unnamed: D13.2, SW13.1
unnamed: D14.2, SW14.1
unnamed: D15.2, SW15.1
unnamed: D16.2, SW16.1
unnamed: D17.2, SW17.1
unnamed: D18.2, SW18.1
unnamed: D19.2, SW19.1
unnamed: D20.2, SW20.1
unnamed: D21.2, SW21.1
unnamed: D22.2, SW22.1
unnamed: D23.2, SW23.1
unnamed: D24.2, SW24.1
unnamed: D25.2, SW25.1
unnamed: D26.2, SW26.1
unnamed: D27.2, SW27.1
unnamed: D28.2, SW28.1
unnamed: D29.2, SW29.1
unnamed: D30.2, SW30.1
unnamed: D31.2, SW31.1
unnamed: D32.2, SW32.1
unnamed: D33.2, SW33.1
unnamed: D34.2, SW34.1
unnamed: D35.2, SW35.1
unnamed: D36.2, SW36.1
unnamed: D37.2, SW37.1
unnamed: D38.2, SW38.1
unnamed: D39.2, SW39.1
unnamed: D40.2, SW40.1
unnamed: D41.2, SW41.1
unnamed: D42.2, SW42.1
unnamed: D43.2, SW43.1
unnamed: D44.2, SW44.1, SW45.1
unnamed: D45.2, SW47.1
unnamed: D46.2, SW48.1
unnamed: D47.2, SW49.1
unnamed: D48.2, SW50.1
unnamed: D49.2, SW51.1
unnamed: D50.2, SW52.1
unnamed: D51.2, SW53.1
unnamed: D52.2, SW54.1
unnamed: D53.2, SW55.1
unnamed: D54.2, SW56.1
unnamed: D55.2, SW57.1
unnamed: D56.2, SW58.1
unnamed: D57.2, SW46.1, SW59.1
unnamed: D58.2, SW60.1
unnamed: D59.2, SW61.1
unnamed: D60.2, SW62.1
unnamed: D61.2, SW63.1
unnamed: D62.2, SW64.1
unnamed: D63.2, SW65.1
unnamed: D64.2, SW66.1
unnamed: D65.2, SW67.1
unnamed: R2.1, U1.32
unnamed: R3.1, U1.33
unnamed: R4.1, U5.47
OSC_IN: C8.1, U1.5, Y1.1
OSC_OUT: C9.1, U1.6, Y1.2
SCL: EXT1.3, R8.2, U1.42, U5.42
SDA: EXT1.2, R9.2, U1.43, U5.41
SWCLK: DBG1.2, U1.37
SWDIO: DBG1.3, U1.34
USART_RX: DBG1.8, U1.31
USART_TX: DBG1.7, U1.30
USB_M: J1.D-, P2.2, R2.2
USB_P: J1.D+, P2.3, R3.2

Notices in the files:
PCBs/stm32_nucleo-64_proto_shield_nucleo_pb/processed.kicad_pcb:
CC BY 4.0 aon@umetronics.com 2015
